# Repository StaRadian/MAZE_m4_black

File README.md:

# MAZE m4 Black README
Langange option: [한국어](README_KR.md)

## LICENSE
```
"THE BEERWARE LICENSE" (Revision 42):
StaRadian wrote this project. As long as you retain this notice,
you can do whatever you want with this stuff. If we meet someday,
and you think this stuff is worth it, you can buy me a beer in return.
```

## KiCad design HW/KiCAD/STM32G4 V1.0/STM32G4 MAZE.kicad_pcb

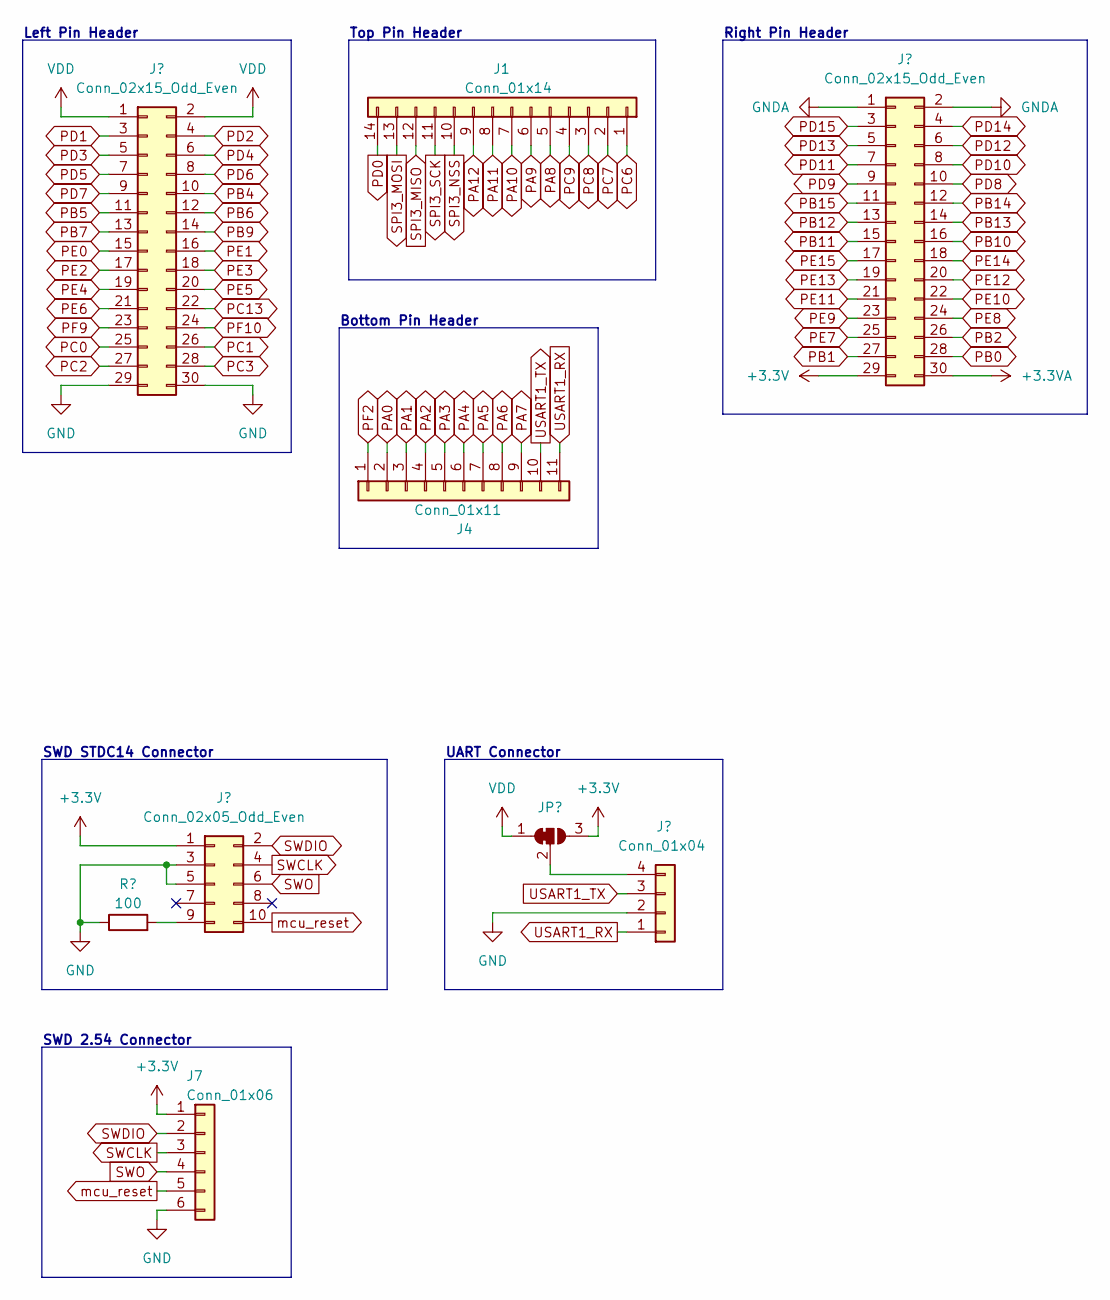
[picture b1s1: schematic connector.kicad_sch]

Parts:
J1: Conn_01x14; PinHeader_1x14_P2.54mm_Vertical
J2: Conn_02x15_Odd_Even; PinHeader_2x15_P2.54mm_Vertical_Right
J3: Conn_02x15_Odd_Even; PinHeader_2x15_P2.54mm_Vertical_Left
J4: Conn_01x11; PinHeader_1x11_P2.54mm_Vertical
J5: Conn_02x05_Odd_Even; SWD
J6: Conn_01x04; Molex_SPOX_5267-04A_1x04_P2.50mm_Vertical
J7: Conn_01x06; PinHeader_1x06_P2.54mm_Vertical
JP3: SolderJumper_3_Bridged12; SolderJumper-3_P1.3mm_Bridged12_RoundedPad1.0x1.5mm
R1: 100; 0603_1608_R_HandSolder

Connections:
+3.3V: J2.29, J5.1, J7.1, JP3.3 (B); also elsewhere on the board
+3.3VA: J2.30; also elsewhere on the board
GND: J3.29, J3.30, J5.3, J5.5, J6.2, J7.6, R1.1; also elsewhere on the board
GNDA: J2.1, J2.2; also elsewhere on the board
unnamed: J5.9, R1.2
unnamed: J6.4, JP3.2 (C)
PA0: J4.2; also elsewhere on the board
PA1: J4.3; also elsewhere on the board
PA2: J4.4; also elsewhere on the board
PA3: J4.5; also elsewhere on the board
PA4: J4.6; also elsewhere on the board
PA5: J4.7; also elsewhere on the board
PA6: J4.8; also elsewhere on the board
PA7: J4.9; also elsewhere on the board
PA8: J1.5; also elsewhere on the board
PA9: J1.6; also elsewhere on the board
PA10: J1.7; also elsewhere on the board
PA11: J1.8; also elsewhere on the board
PA12: J1.9; also elsewhere on the board
PB0: J2.28; also elsewhere on the board
PB1: J2.27; also elsewhere on the board
PB2: J2.26; also elsewhere on the board
PB4: J3.10; also elsewhere on the board
PB5: J3.11; also elsewhere on the board
PB6: J3.12; also elsewhere on the board
PB7: J3.13; also elsewhere on the board
PB9: J3.14; also elsewhere on the board
PB10: J2.16; also elsewhere on the board
PB11: J2.15; also elsewhere on the board
PB12: J2.13; also elsewhere on the board
PB13: J2.14; also elsewhere on the board
PB14: J2.12; also elsewhere on the board
PB15: J2.11; also elsewhere on the board
PC0: J3.25; also elsewhere on the board
PC1: J3.26; also elsewhere on the board
PC2: J3.27; also elsewhere on the board
PC3: J3.28; also elsewhere on the board
PC6: J1.1; also elsewhere on the board
PC7: J1.2; also elsewhere on the board
PC8: J1.3; also elsewhere on the board
PC9: J1.4; also elsewhere on the board
PC13: J3.22; also elsewhere on the board
PD0: J1.14; also elsewhere on the board
PD1: J3.3; also elsewhere on the board
PD2: J3.4; also elsewhere on the board
PD3: J3.5; also elsewhere on the board
PD4: J3.6; also elsewhere on the board
PD5: J3.7; also elsewhere on the board
PD6: J3.8; also elsewhere on the board
PD7: J3.9; also elsewhere on the board
PD8: J2.10; also elsewhere on the board
PD9: J2.9; also elsewhere on the board
PD10: J2.8; also elsewhere on the board
PD11: J2.7; also elsewhere on the board
PD12: J2.6; also elsewhere on the board
PD13: J2.5; also elsewhere on the board
PD14: J2.4; also elsewhere on the board
PD15: J2.3; also elsewhere on the board
PE0: J3.15; also elsewhere on the board
PE1: J3.16; also elsewhere on the board
PE2: J3.17; also elsewhere on the board
PE3: J3.18; also elsewhere on the board
PE4: J3.19; also elsewhere on the board
PE5: J3.20; also elsewhere on the board
PE6: J3.21; also elsewhere on the board
PE7: J2.25; also elsewhere on the board
PE8: J2.24; also elsewhere on the board
PE9: J2.23; also elsewhere on the board
PE10: J2.22; also elsewhere on the board
PE11: J2.21; also elsewhere on the board
PE12: J2.20; also elsewhere on the board
PE13: J2.19; also elsewhere on the board
PE14: J2.18; also elsewhere on the board
PE15: J2.17; also elsewhere on the board
PF2: J4.1; also elsewhere on the board
PF9: J3.23; also elsewhere on the board
PF10: J3.24; also elsewhere on the board
SPI3_MISO: J1.12; also elsewhere on the board
SPI3_MOSI: J1.13; also elsewhere on the board
SPI3_NSS: J1.10; also elsewhere on the board
SPI3_SCK: J1.11; also elsewhere on the board
SWCLK: J5.4, J7.3; also elsewhere on the board
SWDIO: J5.2, J7.2; also elsewhere on the board
SWO: J5.6, J7.4; also elsewhere on the board
USART1_RX: J4.11, J6.1; also elsewhere on the board
USART1_TX: J4.10, J6.3; also elsewhere on the board
VDD: J3.1, J3.2, JP3.1 (A); also elsewhere on the board
mcu_reset: J5.10, J7.5; also elsewhere on the board

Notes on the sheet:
Top Pin Header
SWD STDC14 Connector
Left Pin Header
Bottom Pin Header
UART Connector
Right Pin Header
SWD 2.54 Connector

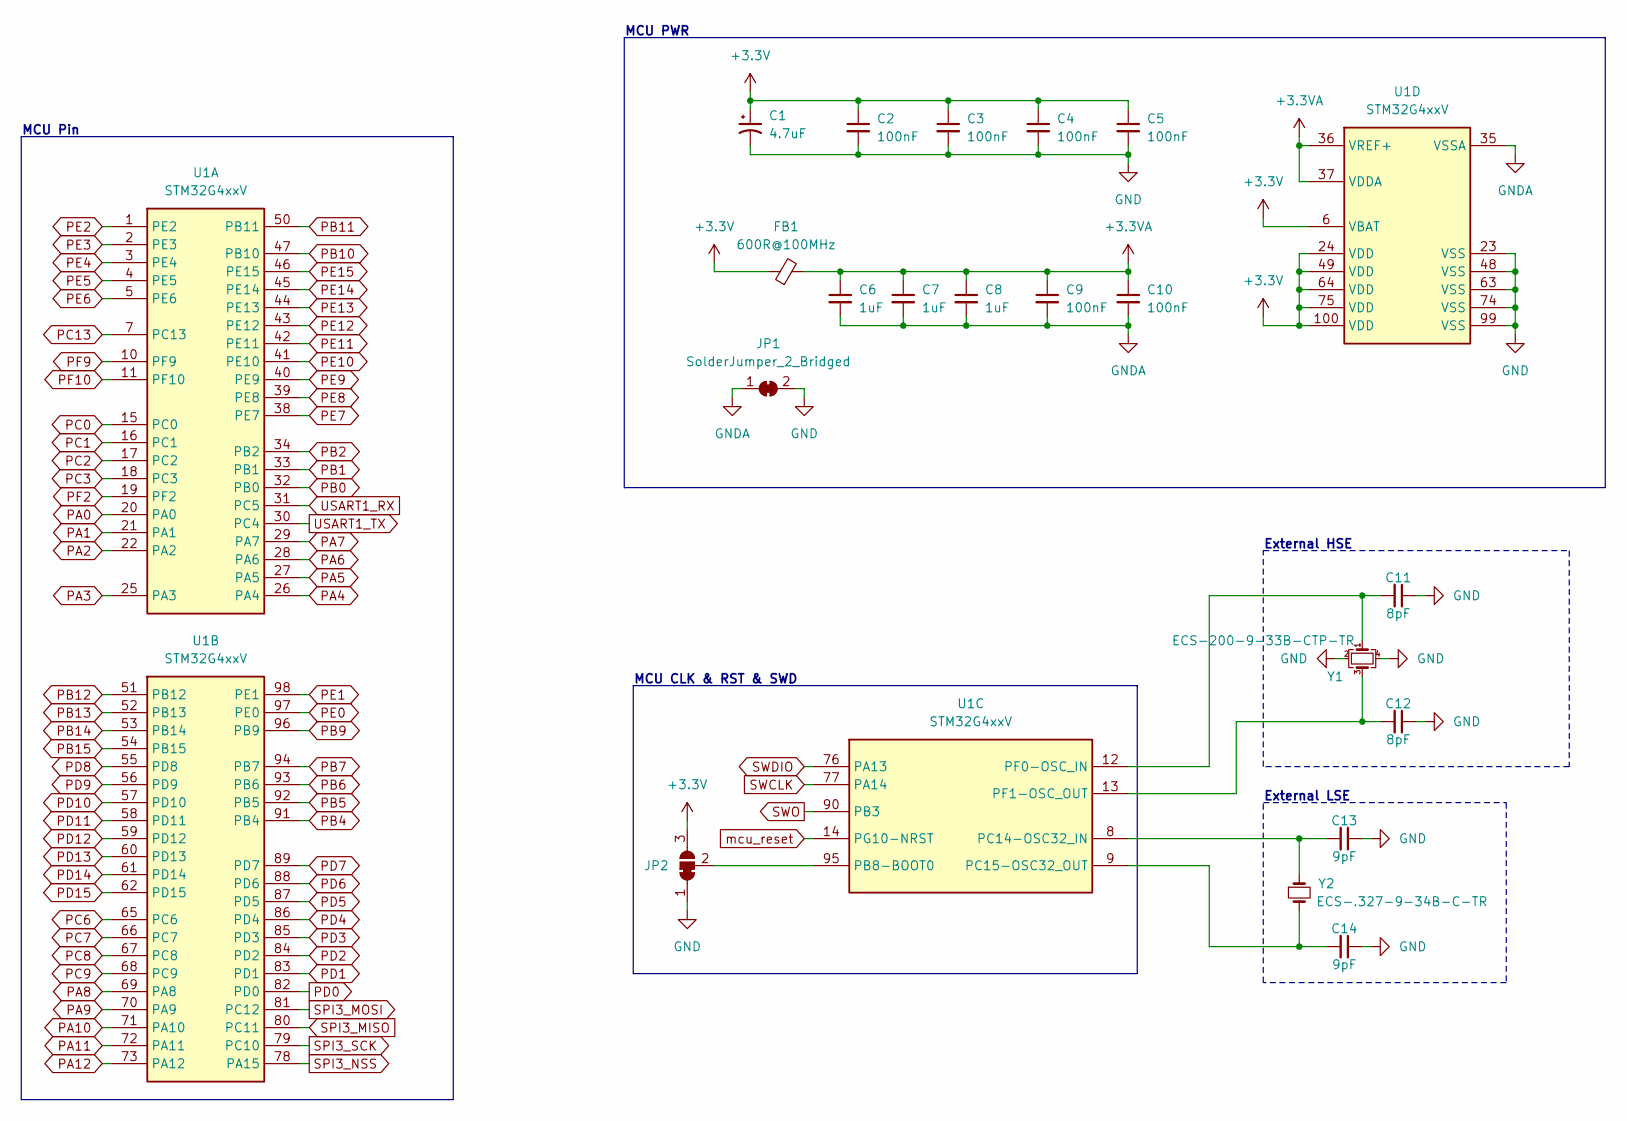
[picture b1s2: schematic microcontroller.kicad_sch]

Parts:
C1: 4.7uF; 1206_3216_C_Polarized_HandSolder
C2, C3, C4, C5, C9, C10: 100nF; 0603_1608_C_HandSolder
C6, C7, C8: 1uF; 0603_1608_C_HandSolder
C11, C12: 8pF; 0603_1608_C_HandSolder
C13, C14: 9pF; 0603_1608_C_HandSolder
FB1: 600R@100MHz; 0603_1608_L_HandSolder
JP1: SolderJumper_2_Bridged; SolderJumper-2_P1.3mm_Bridged_RoundedPad1.0x1.5mm
JP2: SolderJumper_3_Bridged12; SolderJumper-3_P1.3mm_Bridged12_RoundedPad1.0x1.5mm
U1: STM32G4xxV; LQFP-100_14x14mm_P0.5mm
Y1: ECS-200-9-33B-CTP-TR; Crystal_SMD_3225-4Pin_3.2x2.5mm_HandSoldering
Y2: ECS-.327-9-34B-C-TR; Crystal_SMD_3215-2Pin_3.2x1.5mm_HandSoldering

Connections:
+3.3V: C1.1, C2.1, C3.1, C4.1, C5.1, FB1.1, JP2.3 (B), U1.6 (VBAT), U1.24 (VDD), U1.49 (VDD), U1.64 (VDD), U1.75 (VDD), U1.100 (VDD); also elsewhere on the board
+3.3VA: C6.1, C7.1, C8.1, C9.1, C10.1, FB1.2, U1.36 (VREF+), U1.37 (VDDA); also elsewhere on the board
GND: C1.2, C2.2, C3.2, C4.2, C5.2, C11.1, C12.1, C13.1, C14.1, JP1.2 (B), JP2.1 (A), U1.23 (VSS), U1.48 (VSS), U1.63 (VSS), U1.74 (VSS), U1.99 (VSS), Y1.2, Y1.4; also elsewhere on the board
GNDA: C6.2, C7.2, C8.2, C9.2, C10.2, JP1.1 (A), U1.35 (VSSA); also elsewhere on the board
unnamed: JP2.2 (C), U1.95 (PB8-BOOT0)
unnamed: C13.2, U1.8 (PC14-OSC32_IN), Y2.1
unnamed: C14.2, U1.9 (PC15-OSC32_OUT), Y2.2
unnamed: C11.2, U1.12 (PF0-OSC_IN), Y1.1
unnamed: C12.2, U1.13 (PF1-OSC_OUT), Y1.3
PA0: U1.20 (PA0); also elsewhere on the board
PA1: U1.21 (PA1); also elsewhere on the board
PA2: U1.22 (PA2); also elsewhere on the board
PA3: U1.25 (PA3); also elsewhere on the board
PA4: U1.26 (PA4); also elsewhere on the board
PA5: U1.27 (PA5); also elsewhere on the board
PA6: U1.28 (PA6); also elsewhere on the board
PA7: U1.29 (PA7); also elsewhere on the board
PA8: U1.69 (PA8); also elsewhere on the board
PA9: U1.70 (PA9); also elsewhere on the board
PA10: U1.71 (PA10); also elsewhere on the board
PA11: U1.72 (PA11); also elsewhere on the board
PA12: U1.73 (PA12); also elsewhere on the board
PB0: U1.32 (PB0); also elsewhere on the board
PB1: U1.33 (PB1); also elsewhere on the board
PB2: U1.34 (PB2); also elsewhere on the board
PB4: U1.91 (PB4); also elsewhere on the board
PB5: U1.92 (PB5); also elsewhere on the board
PB6: U1.93 (PB6); also elsewhere on the board
PB7: U1.94 (PB7); also elsewhere on the board
PB9: U1.96 (PB9); also elsewhere on the board
PB10: U1.47 (PB10); also elsewhere on the board
PB11: U1.50 (PB11); also elsewhere on the board
PB12: U1.51 (PB12); also elsewhere on the board
PB13: U1.52 (PB13); also elsewhere on the board
PB14: U1.53 (PB14); also elsewhere on the board
PB15: U1.54 (PB15); also elsewhere on the board
PC0: U1.15 (PC0); also elsewhere on the board
PC1: U1.16 (PC1); also elsewhere on the board
PC2: U1.17 (PC2); also elsewhere on the board
PC3: U1.18 (PC3); also elsewhere on the board
PC6: U1.65 (PC6); also elsewhere on the board
PC7: U1.66 (PC7); also elsewhere on the board
PC8: U1.67 (PC8); also elsewhere on the board
PC9: U1.68 (PC9); also elsewhere on the board
PC13: U1.7 (PC13); also elsewhere on the board
PD0: U1.82 (PD0); also elsewhere on the board
PD1: U1.83 (PD1); also elsewhere on the board
PD2: U1.84 (PD2); also elsewhere on the board
PD3: U1.85 (PD3); also elsewhere on the board
PD4: U1.86 (PD4); also elsewhere on the board
PD5: U1.87 (PD5); also elsewhere on the board
PD6: U1.88 (PD6); also elsewhere on the board
PD7: U1.89 (PD7); also elsewhere on the board
PD8: U1.55 (PD8); also elsewhere on the board
PD9: U1.56 (PD9); also elsewhere on the board
PD10: U1.57 (PD10); also elsewhere on the board
PD11: U1.58 (PD11); also elsewhere on the board
PD12: U1.59 (PD12); also elsewhere on the board
PD13: U1.60 (PD13); also elsewhere on the board
PD14: U1.61 (PD14); also elsewhere on the board
PD15: U1.62 (PD15); also elsewhere on the board
PE0: U1.97 (PE0); also elsewhere on the board
PE1: U1.98 (PE1); also elsewhere on the board
PE2: U1.1 (PE2); also elsewhere on the board
PE3: U1.2 (PE3); also elsewhere on the board
PE4: U1.3 (PE4); also elsewhere on the board
PE5: U1.4 (PE5); also elsewhere on the board
PE6: U1.5 (PE6); also elsewhere on the board
PE7: U1.38 (PE7); also elsewhere on the board
PE8: U1.39 (PE8); also elsewhere on the board
PE9: U1.40 (PE9); also elsewhere on the board
PE10: U1.41 (PE10); also elsewhere on the board
PE11: U1.42 (PE11); also elsewhere on the board
PE12: U1.43 (PE12); also elsewhere on the board
PE13: U1.44 (PE13); also elsewhere on the board
PE14: U1.45 (PE14); also elsewhere on the board
PE15: U1.46 (PE15); also elsewhere on the board
PF2: U1.19 (PF2); also elsewhere on the board
PF9: U1.10 (PF9); also elsewhere on the board
PF10: U1.11 (PF10); also elsewhere on the board
SPI3_MISO: U1.80 (PC11); also elsewhere on the board
SPI3_MOSI: U1.81 (PC12); also elsewhere on the board
SPI3_NSS: U1.78 (PA15); also elsewhere on the board
SPI3_SCK: U1.79 (PC10); also elsewhere on the board
SWCLK: U1.77 (PA14); also elsewhere on the board
SWDIO: U1.76 (PA13); also elsewhere on the board
SWO: U1.90 (PB3); also elsewhere on the board
USART1_RX: U1.31 (PC5); also elsewhere on the board
USART1_TX: U1.30 (PC4); also elsewhere on the board
mcu_reset: U1.14 (PG10-NRST); also elsewhere on the board

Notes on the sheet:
MCU CLK & RST & SWD
External HSE
External LSE
MCU PWR
MCU Pin

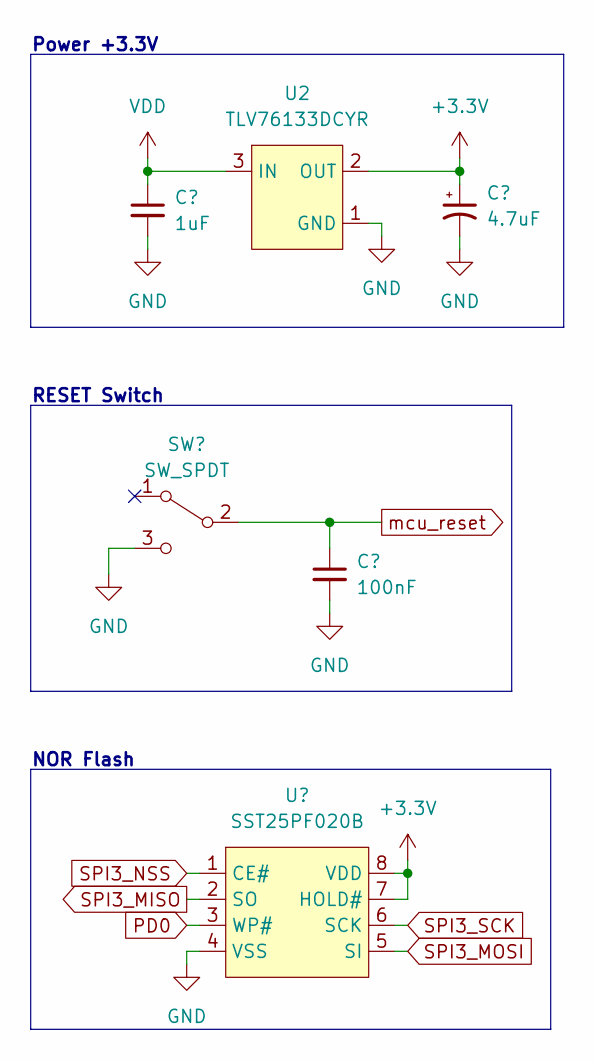
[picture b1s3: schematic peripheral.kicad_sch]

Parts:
C15: 1uF; 0603_1608_C_HandSolder
C16: 4.7uF; 1206_3216_C_Polarized_HandSolder
C17: 100nF; 0603_1608_C_HandSolder
SW1: SW_SPDT; SW_Micro
U2: TLV76133DCYR; SOT-223
U3: SST25PF020B; SOIC-8_5x6mm_P1.27mm

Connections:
+3.3V: C16.1, U2.2 (OUT), U3.7 (HOLD#), U3.8 (VDD); also elsewhere on the board
GND: C15.2, C16.2, C17.2, SW1.3 (C), U2.1 (GND), U3.4 (VSS); also elsewhere on the board
PD0: U3.3 (WP#); also elsewhere on the board
SPI3_MISO: U3.2 (SO); also elsewhere on the board
SPI3_MOSI: U3.5 (SI); also elsewhere on the board
SPI3_NSS: U3.1 (CE#); also elsewhere on the board
SPI3_SCK: U3.6 (SCK); also elsewhere on the board
VDD: C15.1, U2.3 (IN); also elsewhere on the board
mcu_reset: C17.1, SW1.2 (B); also elsewhere on the board

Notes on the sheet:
RESET Switch
NOR Flash
Power +3.3V

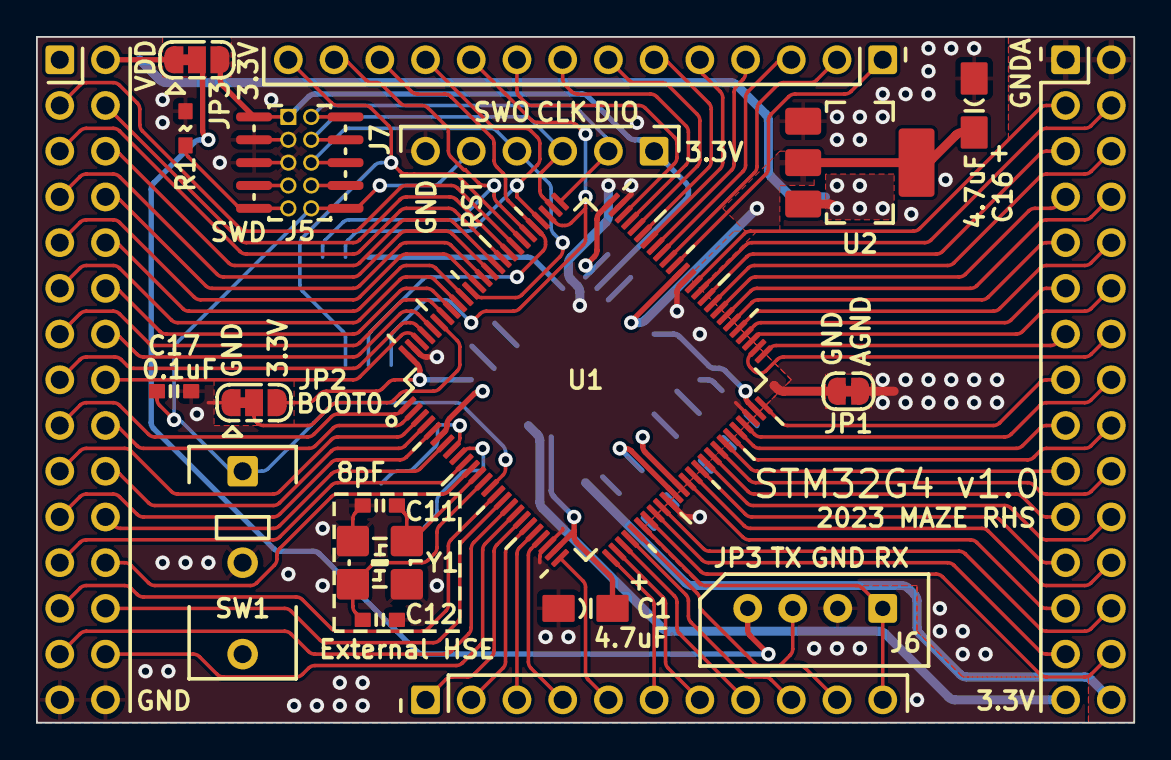
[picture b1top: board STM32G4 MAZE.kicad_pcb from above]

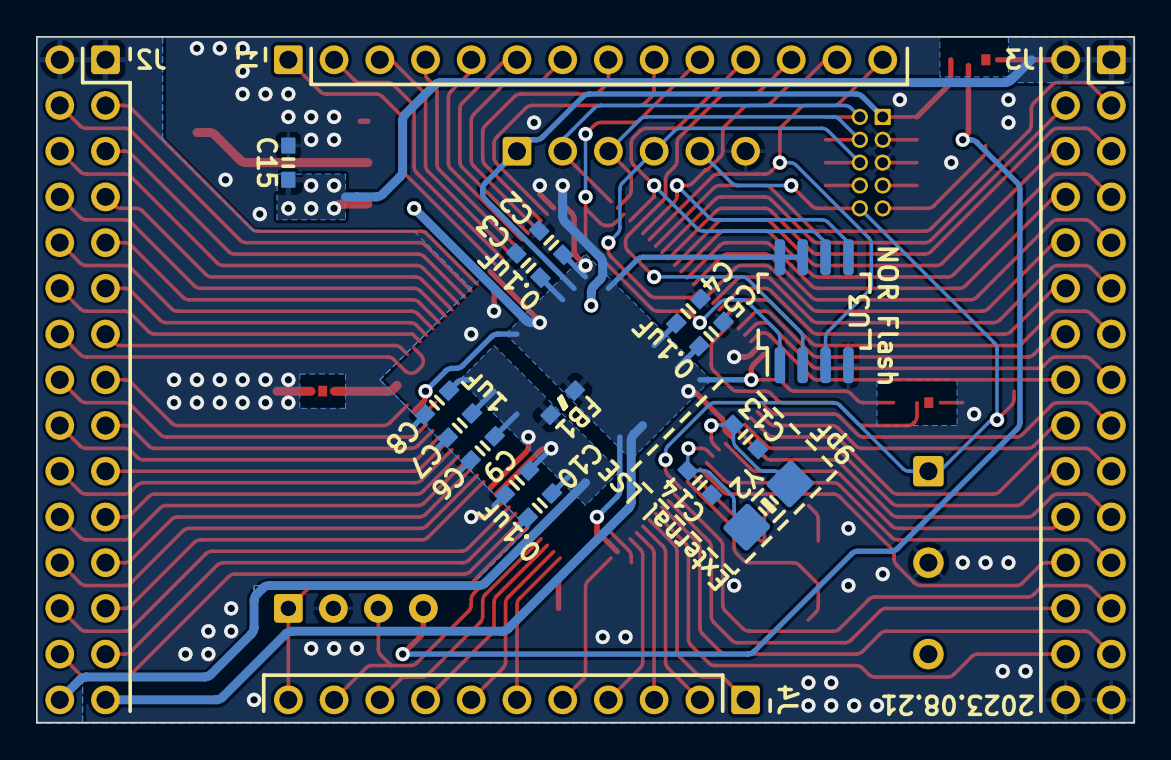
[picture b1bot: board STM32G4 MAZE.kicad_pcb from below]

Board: 2 copper layers, 61.0 x 38.1 mm, 35 parts (15 on the bottom side), 93 nets.

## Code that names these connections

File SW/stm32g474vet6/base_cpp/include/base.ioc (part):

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Mcu.Name=STM32G474V(B-C-E)Tx
Mcu.Package=LQFP100
Mcu.UserName=STM32G474VETx
PA10.Mode=Output_TB1
PA10.Signal=HRTIM1_CHB1
PA13.Mode=Trace_Asynchronous_SW
PA13.Signal=SYS_JTMS-SWDIO
PA14.Mode=Trace_Asynchronous_SW
PA14.Signal=SYS_JTCK-SWCLK
PA15.GPIOParameters=PinState,GPIO_Label
PA15.GPIO_Label=Flash_CE
PA15.PinState=GPIO_PIN_SET
PA15.Signal=GPIO_Output
PA4.GPIOParameters=PinState
PA4.PinState=GPIO_PIN_SET
PA4.Signal=GPIO_Output
PA5.Mode=Full_Duplex_Master
PA5.Signal=SPI1_SCK
PA6.Mode=Full_Duplex_Master
PA6.Signal=SPI1_MISO
PA7.Mode=Full_Duplex_Master
PA7.Signal=SPI1_MOSI
PA8.Mode=Output_TA1
PA8.Signal=HRTIM1_CHA1
PB3.Mode=Trace_Asynchronous_SW
PB3.Signal=SYS_JTDO-SWO
PB6.Signal=GPIO_Output
PB7.Signal=GPIO_Output
PB9.Signal=GPIO_Output
PC10.GPIOParameters=GPIO_PuPd
PC10.GPIO_PuPd=GPIO_PULLDOWN
PC10.Mode=Full_Duplex_Master
PC10.Signal=SPI3_SCK
PC11.Mode=Full_Duplex_Master
PC11.Signal=SPI3_MISO
PC12.Mode=Full_Duplex_Master
PC12.Signal=SPI3_MOSI
PC14-OSC32_IN.Mode=LSE-External-Oscillator
PC14-OSC32_IN.Signal=RCC_OSC32_IN
PC15-OSC32_OUT.Mode=LSE-External-Oscillator
PC15-OSC32_OUT.Signal=RCC_OSC32_OUT
PC5.Mode=Asynchronous
PC5.Signal=USART1_RX
PC8.Mode=I2C
PC8.Signal=I2C3_SCL
PC9.Mode=I2C
PC9.Signal=I2C3_SDA
PD0.Signal=GPIO_Output
PD0.Stacked=true
PE0.Mode=Asynchronous
PE0.Signal=USART1_TX
PE4.Signal=GPIO_Output
PE5.Signal=GPIO_Output
PE6.Signal=GPIO_Output
PF0-OSC_IN.Mode=HSE-External-Oscillator
PF0-OSC_IN.Signal=RCC_OSC_IN
PF1-OSC_OUT.Mode=HSE-External-Oscillator
PF1-OSC_OUT.Signal=RCC_OSC_OUT
RCC.HSE_VALUE=20000000
RCC.SYSCLKFreq_VALUE=170000000
RCC.SYSCLKSource=RCC_SYSCLKSOURCE_PLLCLK
board=custom

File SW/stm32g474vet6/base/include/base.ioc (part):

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Mcu.Name=STM32G474V(B-C-E)Tx
Mcu.Package=LQFP100
Mcu.UserName=STM32G474VETx
PA13.Mode=Trace_Asynchronous_SW
PA13.Signal=SYS_JTMS-SWDIO
PA14.Mode=Trace_Asynchronous_SW
PA14.Signal=SYS_JTCK-SWCLK
PA15.Mode=NSS_Signal_Hard_Output
PA15.Signal=SPI3_NSS
PA15.Stacked=true
PA4.Mode=NSS_Signal_Hard_Output
PA4.Signal=SPI1_NSS
PA5.Mode=Full_Duplex_Master
PA5.Signal=SPI1_SCK
PA6.Mode=Full_Duplex_Master
PA6.Signal=SPI1_MISO
PA7.Mode=Full_Duplex_Master
PA7.Signal=SPI1_MOSI
PB3.Mode=Trace_Asynchronous_SW
PB3.Signal=SYS_JTDO-SWO
PB6.Signal=GPIO_Output
PB7.Signal=GPIO_Output
PB9.Signal=GPIO_Output
PC10.Mode=Full_Duplex_Master
PC10.Signal=SPI3_SCK
PC11.Mode=Full_Duplex_Master
PC11.Signal=SPI3_MISO
PC12.Mode=Full_Duplex_Master
PC12.Signal=SPI3_MOSI
PC14-OSC32_IN.Mode=LSE-External-Oscillator
PC14-OSC32_IN.Signal=RCC_OSC32_IN
PC15-OSC32_OUT.Mode=LSE-External-Oscillator
PC15-OSC32_OUT.Signal=RCC_OSC32_OUT
PC4.Mode=Asynchronous
PC4.Signal=USART1_TX
PC5.Mode=Asynchronous
PC5.Signal=USART1_RX
PD0.GPIOParameters=GPIO_Label
PD0.GPIO_Label=Flash_WP
PD0.Signal=GPIO_Output
PD0.Stacked=true
PE4.Signal=GPIO_Output
PE5.Signal=GPIO_Output
PE6.Signal=GPIO_Output
PF0-OSC_IN.Mode=HSE-External-Oscillator
PF0-OSC_IN.Signal=RCC_OSC_IN
PF1-OSC_OUT.Mode=HSE-External-Oscillator
PF1-OSC_OUT.Signal=RCC_OSC_OUT
RCC.HSE_VALUE=20000000
RCC.SYSCLKFreq_VALUE=170000000
RCC.SYSCLKSource=RCC_SYSCLKSOURCE_PLLCLK
board=custom

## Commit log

2023-08-26 add readme file
2023-08-26 delete
2023-08-26 sch pdf add
2023-09-02 first working
2023-11-02 add: readme
2023-11-02 add: main
2023-11-02 add: cubemx project
2023-11-02 add: cmake
2023-11-02 add: vscode json
2023-11-02 delete: junk
2023-11-02 change: readme
2023-11-02 add: extensions.json
2023-11-03 update: file move
2023-11-03 update: main
2023-11-03 delete: file move
2023-11-03 update: setting
2023-11-03 add: hcms bit bang
2023-11-06 add: README.md
2023-11-06 update: hcmsprintf -> hcmsprint
2023-11-29 add: c++ test
2023-11-29 add: hc-06 control
2023-11-29 what is this file?
2023-11-29 change: update json
2023-11-29 add: test c++ project
2023-11-29 change: c++ test
2023-11-29 change: add comment
2023-11-29 change: main test
2023-12-02 change: main.cpp -> Main.cpp
2023-12-02 add: c++ project
2023-12-02 change: flash features
2023-12-02 add: const
2023-12-02 add: uartprint
2023-12-05 change: const char *
2023-12-05 auto: cstring?
2023-12-05 move file: main -> core
2023-12-05 change: spi3_nss -> gpio
2023-12-11 update: add clt path
2023-12-11 update: nothing
2023-12-11 add: vscode
2023-12-12 making test branch
2024-01-01 add: gitignore
2024-01-06 update: stm32g473
